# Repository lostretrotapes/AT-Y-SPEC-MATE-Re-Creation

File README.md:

# AT-Y-SPEC-MATE-Re-Creation

This is a copy of the recreation that used be hosted at http://projectspeccy.com/projects/ with permission from Steve Smith

Back in the heyday of the Sinclair Spectrum and other 8-bit computers that kick started the home computing movement, I owned a Sinclair Spectrum 48K Plus that I upgraded from my original rubber key Spectrum with a kit from Sinclair. Along with my friends help, I used to hack games for infinite lives etc. This was a very common practice made easier by certian interfaces. The interfaces would freeze the game/program you were running and allow it to be saved to some sort of media, Tape, Sinclair’s own Microdrive or floppy disc for example.

Of course, these interfaces were quite expensive and above the budget of your average schoolboy hacker! I used to hack long-hand, that is to say, from the loader up. Some programs defeated my limited knowledge. Handily though, I had a friend who was into computers and had a more affluent family than I. He got a SPEC-MATE for his birthday. Later on, he loaned it to me so I could capture my game collection to Tape/Microdrive. This was a revelation! And one of the really useful features was that the SPEC-MATE made two files of main memory. This meant that you could load a dissassembler into one part of memory and a half of the programs code in the other. Hacking became exponentially easier!

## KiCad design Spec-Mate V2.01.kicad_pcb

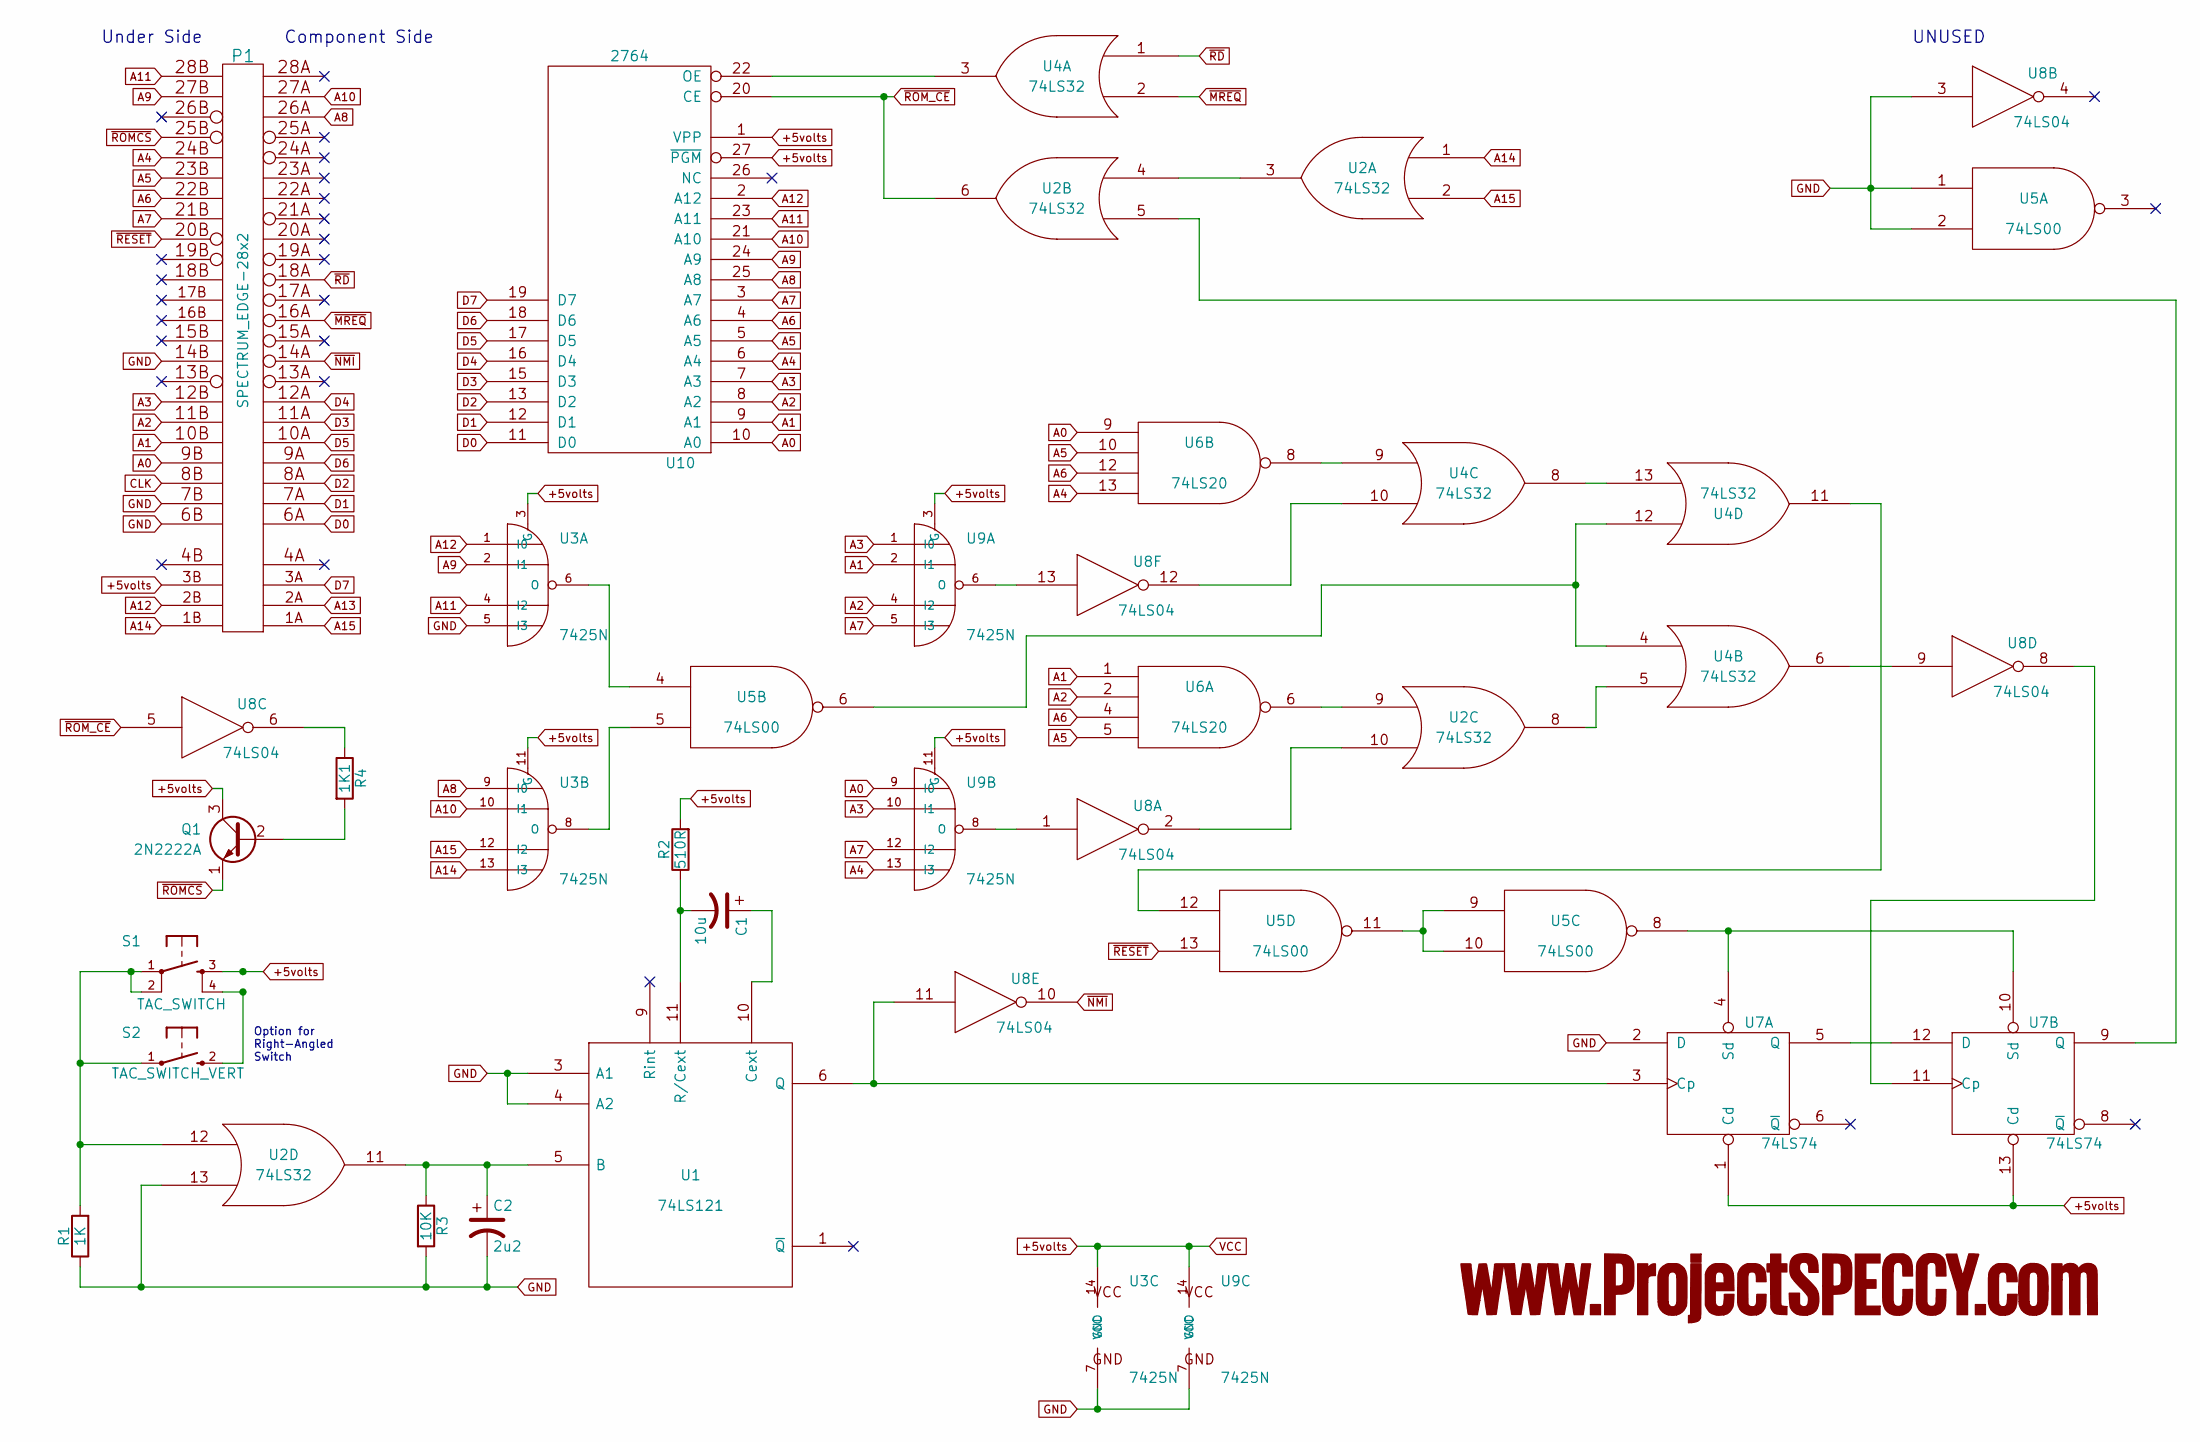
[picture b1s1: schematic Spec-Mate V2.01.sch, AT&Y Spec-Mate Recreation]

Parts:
C1: 10u; CP_Radial_D5.0mm_P2.50mm
C2: 2u2; CP_Radial_D5.0mm_P2.50mm
P1: SPECTRUM_EDGE-28x2; Spectrum_Edge_Connector
Q1: 2N2222A; TO-92_Inline_Narrow_Oval
R1: 1K; R_Axial_DIN0204_L3.6mm_D1.6mm_P5.08mm_Horizontal
R2: 510R; R_Axial_DIN0204_L3.6mm_D1.6mm_P5.08mm_Horizontal
R3: 10K; R_Axial_DIN0204_L3.6mm_D1.6mm_P5.08mm_Horizontal
R4: 1K1; R_Axial_DIN0204_L3.6mm_D1.6mm_P5.08mm_Horizontal
S1: TAC_SWITCH; TACTILE-PTH
S2: TAC_SWITCH_VERT; SW_Tactile_SPST_Angled_PTS645Vx58-2LFS
U1: 74LS121; DIP-14_W7.62mm_LongPads
U2, U4: 74LS32; DIP-14_W7.62mm_LongPads
U3, U9: 7425N; DIP-14_W7.62mm_LongPads
U5: 74LS00; DIP-14_W7.62mm_LongPads
U6: 74LS20; DIP-14_W7.62mm_LongPads
U7: 74LS74; DIP-14_W7.62mm_LongPads
U8: 74LS04; DIP-14_W7.62mm_LongPads
U10: 2764; DIP-28_W15.24mm_LongPads

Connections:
+5volts: P1.3B (+5volts), Q1.3 (C), R2.2, S1.3, U1.14 (VCC), U2.14 (VCC), U3.3 (G), U3.11 (G), U3.14 (VCC), U4.14 (VCC), U5.14 (VCC), U6.14 (VCC), U7.1 (Cd), U7.13 (Cd), U7.14 (VCC), U8.14 (VCC), U9.3 (G), U9.11 (G), U9.14 (VCC), U10.1 (VPP), U10.27 (~PGM), U10.28 (VCC)
A0: P1.9B (A0), U6.9, U9.9 (I0), U10.10 (A0)
A1: P1.10B (A1), U6.1, U9.2 (I1), U10.9 (A1)
A2: P1.11B (A2), U6.2, U9.4 (I2), U10.8 (A2)
A3: P1.12B (A3), U9.1 (I0), U9.10 (I1), U10.7 (A3)
A4: P1.24B (A4), U6.13, U9.13 (I3), U10.6 (A4)
A5: P1.23B (A5), U6.5, U6.10, U10.5 (A5)
A6: P1.22B (A6), U6.4, U6.12, U10.4 (A6)
A7: P1.21B (A7), U9.5 (I3), U9.12 (I2), U10.3 (A7)
A8: P1.26A (A8), U3.9 (I0), U10.25 (A8)
A9: P1.27B (A9), U3.2 (I1), U10.24 (A9)
A10: P1.27A (A10), U3.10 (I1), U10.21 (A10)
A11: P1.28B (A11), U3.4 (I2), U10.23 (A11)
A12: P1.2B (A12), U3.1 (I0), U10.2 (A12)
A13: P1.2A (A13)
A14: P1.1B (A14), U2.1, U3.13 (I3)
A15: P1.1A (A15), U2.2, U3.12 (I2)
CLK: P1.8B (CLK)
D0: P1.6A (D0), U10.11 (D0)
D1: P1.7A (D1), U10.12 (D1)
D2: P1.8A (D2), U10.13 (D2)
D3: P1.11A (D3), U10.15 (D3)
D4: P1.12A (D4), U10.16 (D4)
D5: P1.10A (D5), U10.17 (D5)
D6: P1.9A (D6), U10.18 (D6)
D7: P1.3A (D7), U10.19 (D7)
GND: C2.2, P1.6B (GND), P1.7B (GND), P1.14B (GND), R1.1, R3.2, U1.3 (A1), U1.4 (A2), U1.7 (GND), U2.7 (GND), U2.13, U3.5 (I3), U3.7 (GND), U4.7 (GND), U5.1, U5.2, U5.7 (GND), U6.7 (GND), U7.2 (D), U7.7 (GND), U8.3, U8.7 (GND), U9.7 (GND), U10.14 (GND)
unnamed: C1.1, U1.10 (Cext)
unnamed: C1.2, R2.1, U1.11 (R/Cext)
unnamed: C2.1, R3.1, U1.5 (B), U2.11
unnamed: Q1.2 (B), R4.2
unnamed: R1.2, S1.1, S1.2, S2.1, U2.12
unnamed: R4.1, U8.6
unnamed: S1.4, S2.2
unnamed: U1.6 (Q), U7.3 (Cp), U8.11
unnamed: U2.3, U2.4
unnamed: U2.5, U7.9 (Q)
unnamed: U2.8, U4.5
unnamed: U2.9, U6.6
unnamed: U2.10, U8.2
unnamed: U3.6 (O), U5.4
unnamed: U3.8 (O), U5.5
unnamed: U4.6, U8.9
unnamed: U4.9, U6.8
unnamed: U4.10, U8.12
unnamed: U4.11, U5.12
unnamed: U4.4, U4.12, U5.6
unnamed: U4.8, U4.13
unnamed: U5.8, U7.4 (Sd), U7.10 (Sd)
unnamed: U5.9, U5.10, U5.11
unnamed: U7.11 (Cp), U8.8
unnamed: U7.5 (Q), U7.12 (D)
unnamed: U8.1, U9.8 (O)
unnamed: U8.13, U9.6 (O)
unnamed: U4.3, U10.22 (OE)
~MREQ: P1.16A (~MREQ), U4.2
~NMI: P1.14A (~NMI), U8.10
~RD: P1.18A (~RD), U4.1
~RESET: P1.20B (~RESET), U5.13
~ROMCS: P1.25B (~ROMCS), Q1.1 (E)
~ROM_CE: U2.6, U8.5, U10.20 (CE)

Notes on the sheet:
Under Side
Component Side
UNUSED
Option for Right-Angled Switch

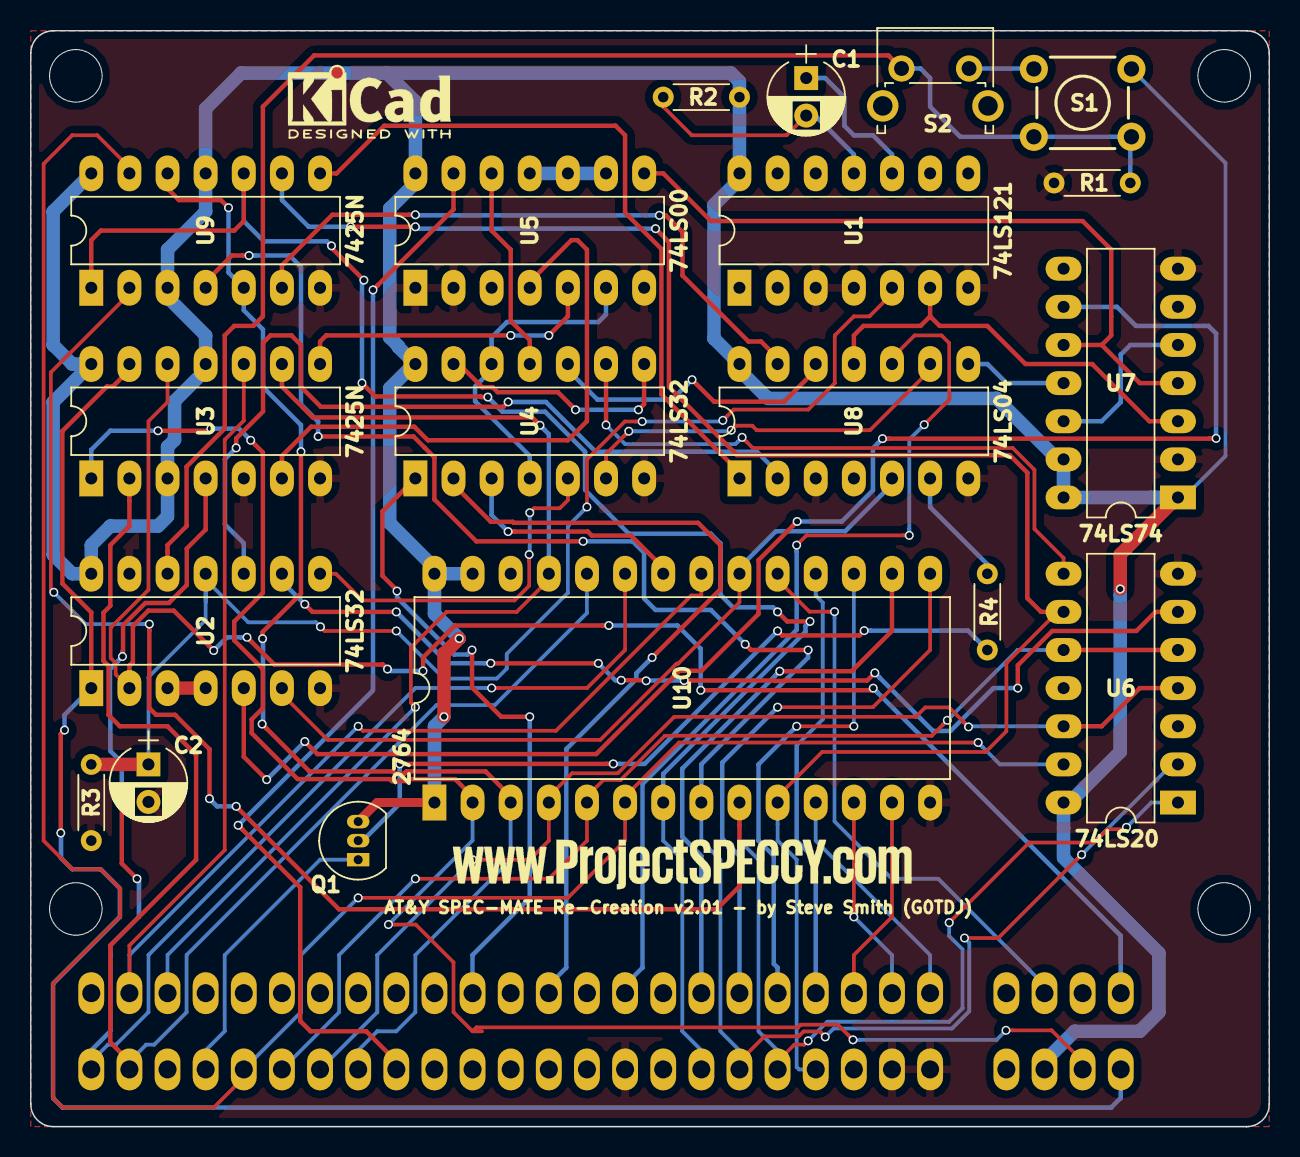
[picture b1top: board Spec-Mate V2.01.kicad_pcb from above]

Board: 2 copper layers, 82.5 x 73.0 mm, 20 parts (1 on the bottom side), 59 nets.

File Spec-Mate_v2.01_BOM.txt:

Recreated AT&Y SPEC-MATE v2.01

Bill Of Materials

R1	1x 1K 1/4W Resistor
R2	1x 510R 1/4W Resistor
R3	1x 10K 1/4W Resistor
R4	1x 1K1 1/4W Resistor
C1	1x 10u 25v Electrolytic Capacitor
C2	1x 2u2 Electrolytic Capacitor

U1	1x 74LS121
U2/4	2x 74LS32
U3/9	2x SN7425
U5	1x 74LS00
U6	1x 74LS20
U7	1x 74LS74
U8	1x 74LS04
U10	1x 2764 EPROM

Q1	1x 2N2222A Transistor

S1	1x Horizontal Tact Switch (Optional)
S2	1x Right Angle Tact Switch

P1	1x 28x2 Pin Spectrum Edge Connector with slot in pos. 5.

*** www.ProjectSPECCY.com ***
